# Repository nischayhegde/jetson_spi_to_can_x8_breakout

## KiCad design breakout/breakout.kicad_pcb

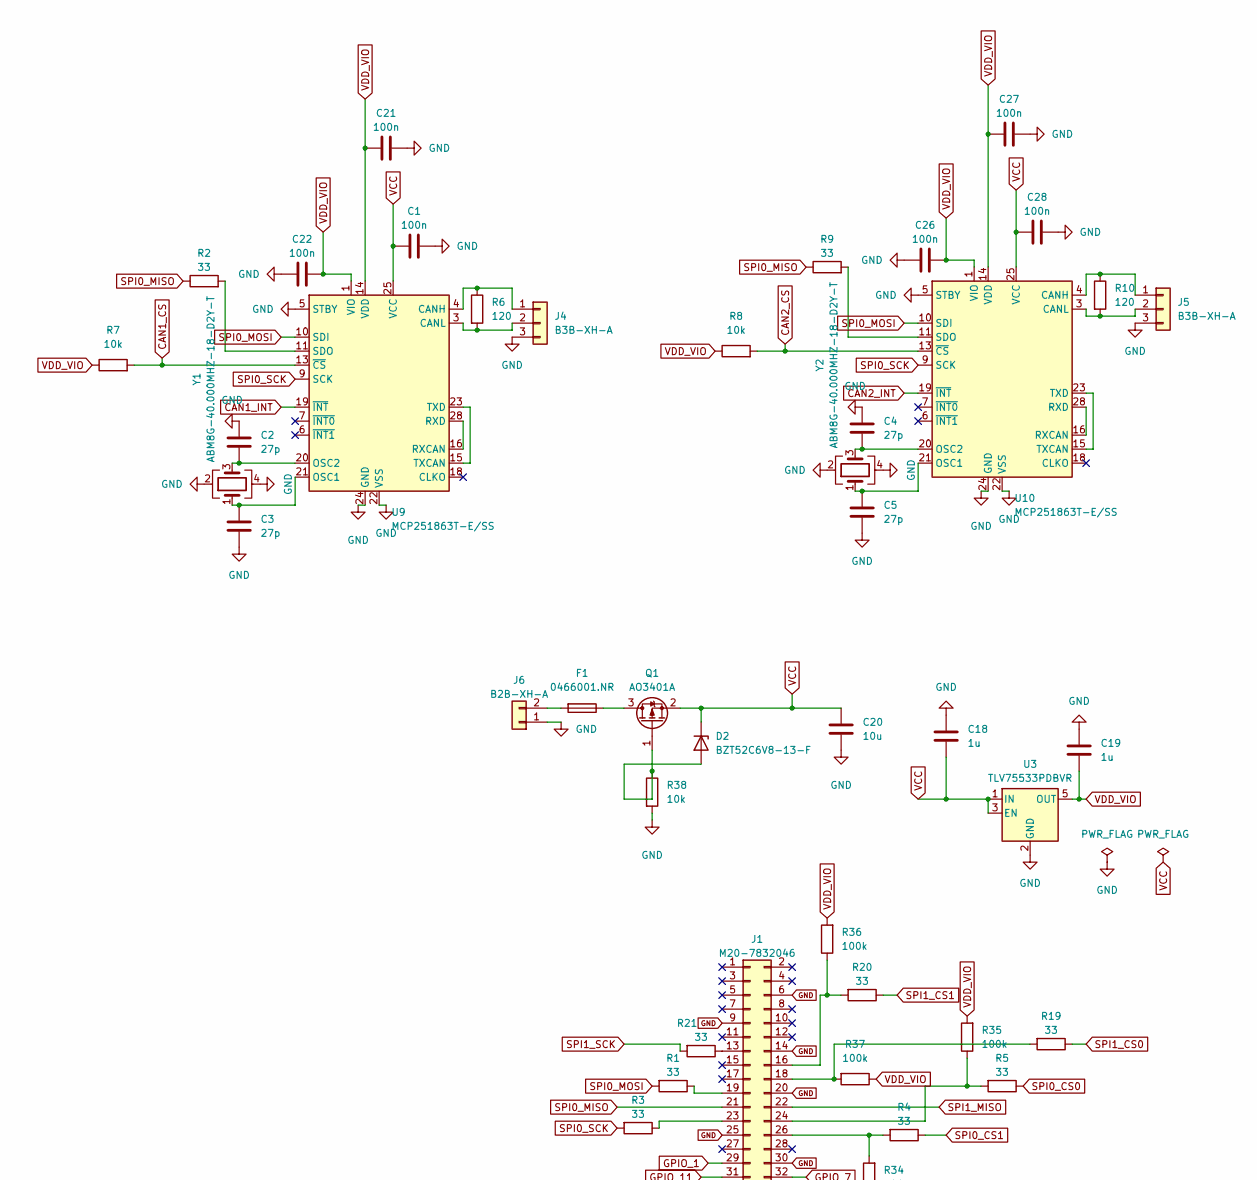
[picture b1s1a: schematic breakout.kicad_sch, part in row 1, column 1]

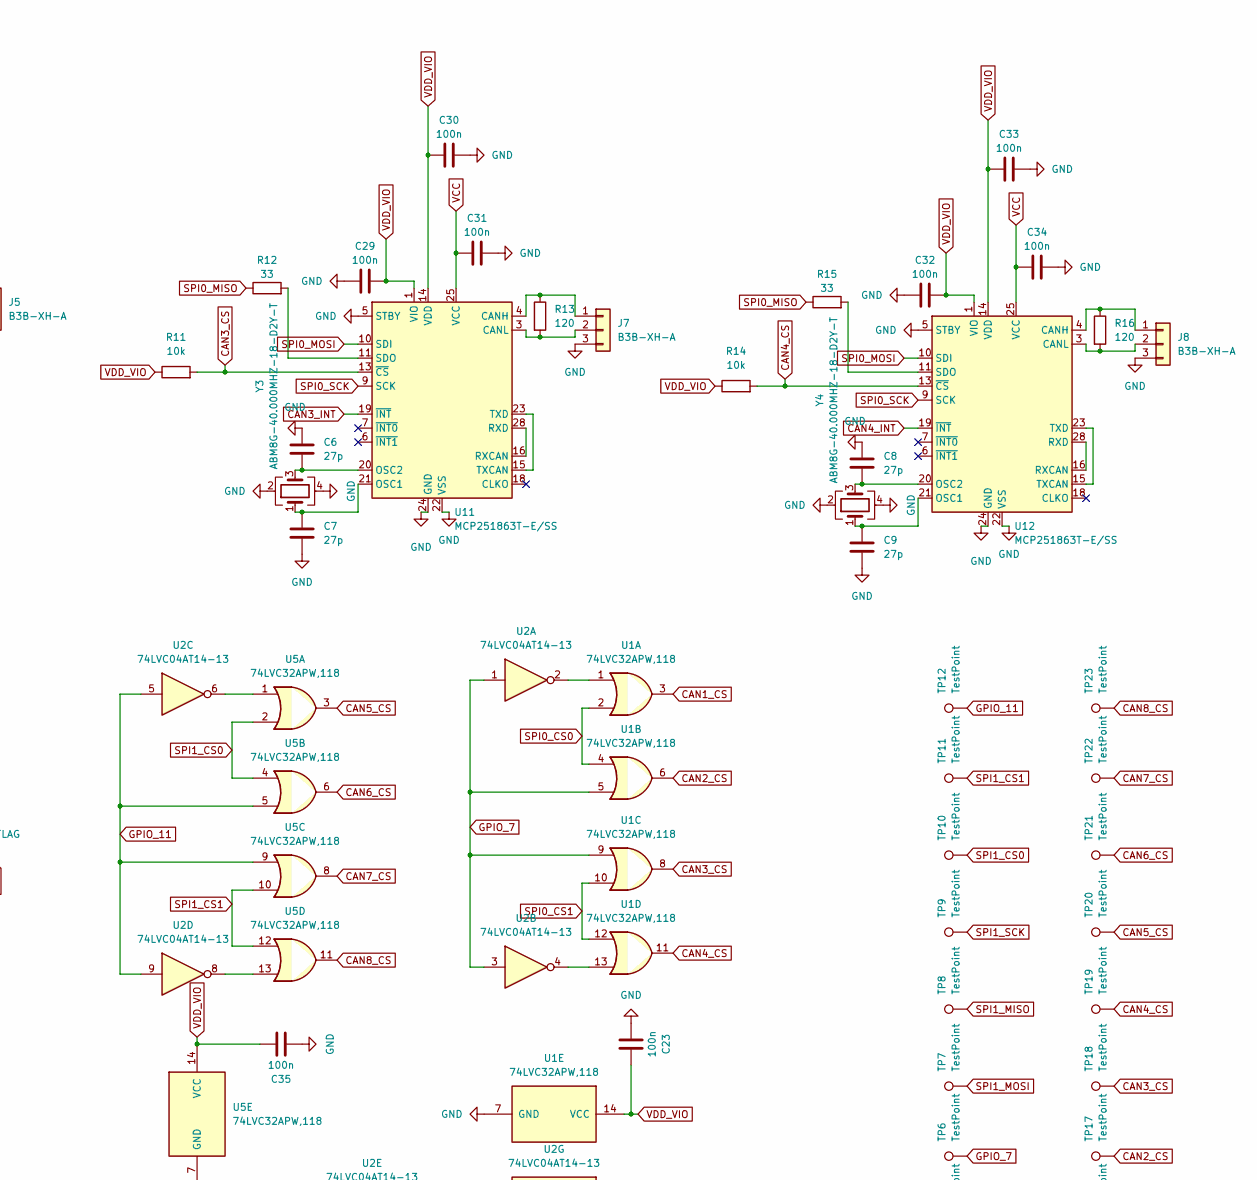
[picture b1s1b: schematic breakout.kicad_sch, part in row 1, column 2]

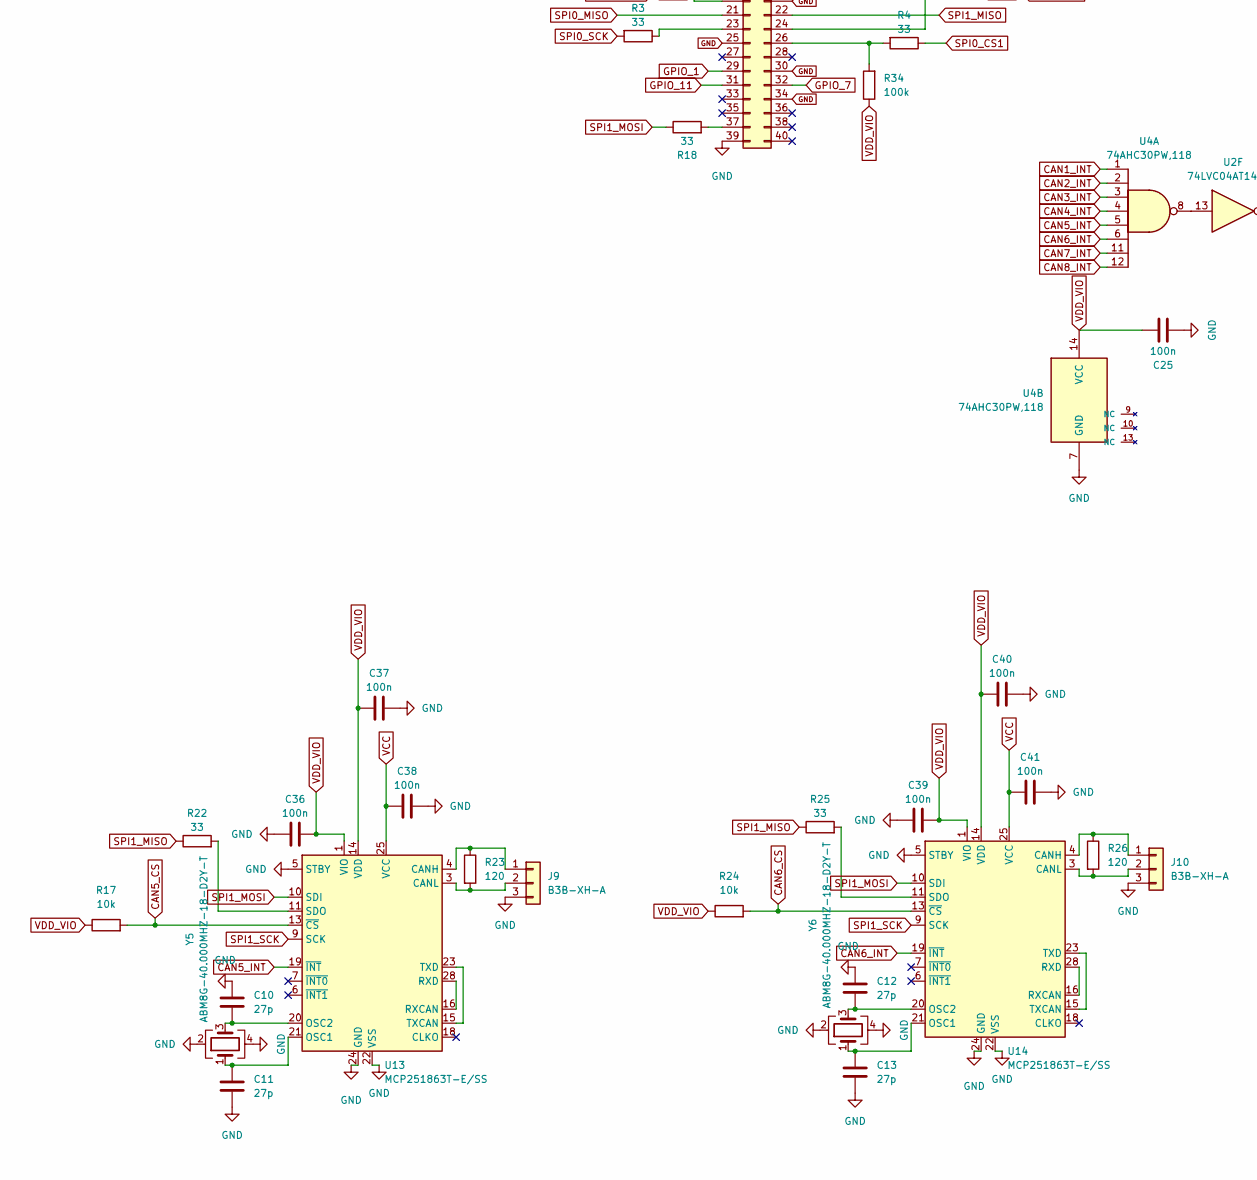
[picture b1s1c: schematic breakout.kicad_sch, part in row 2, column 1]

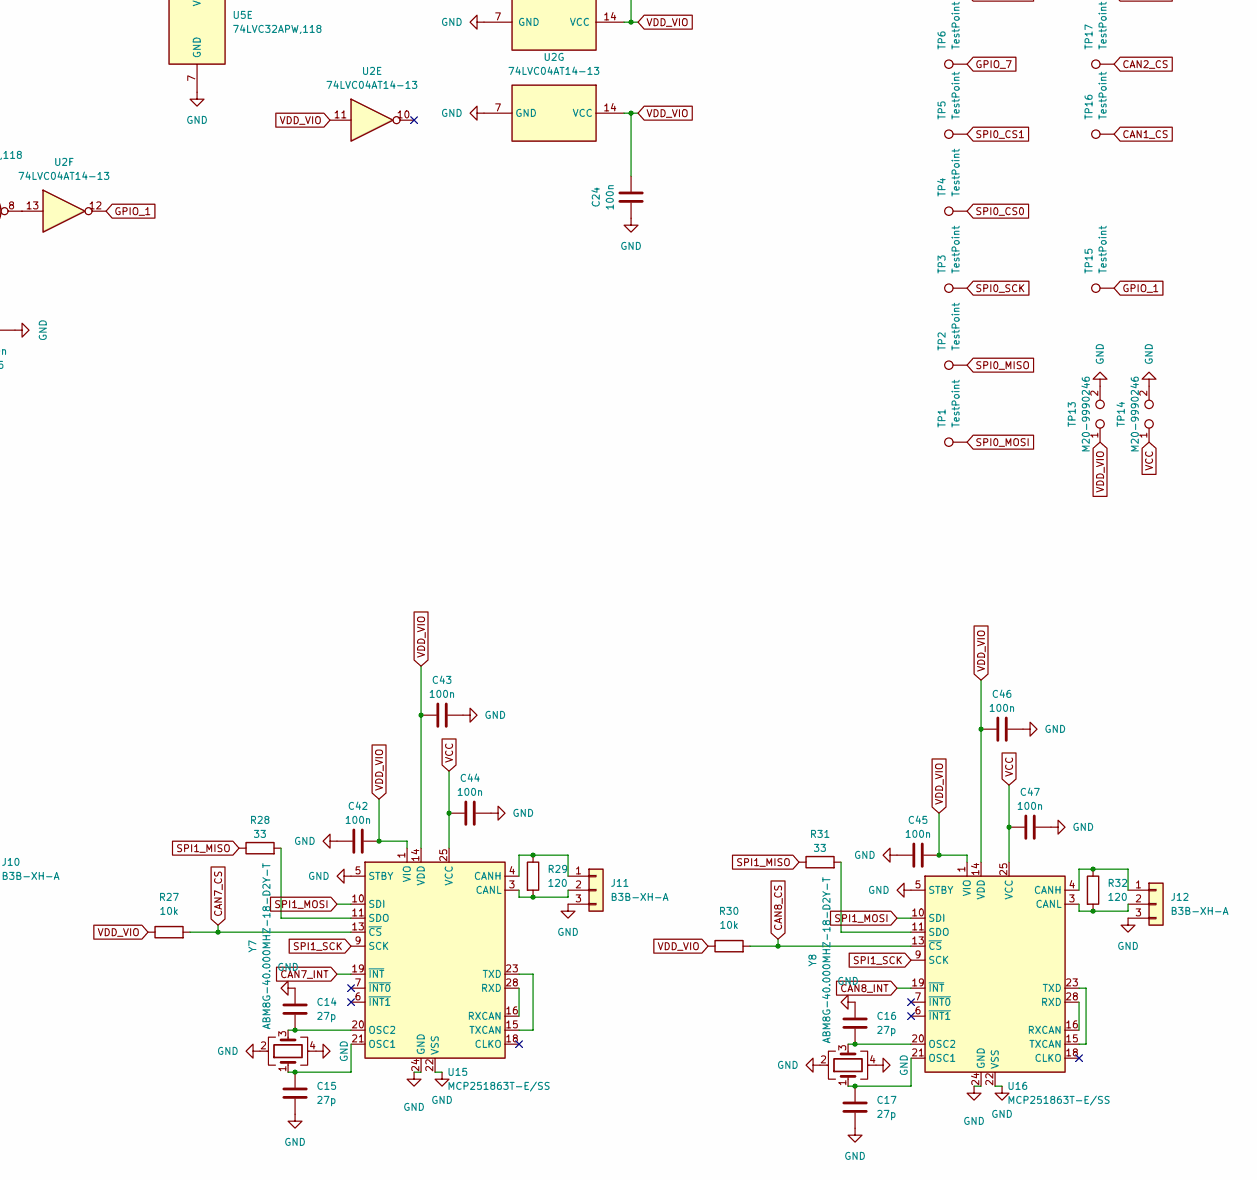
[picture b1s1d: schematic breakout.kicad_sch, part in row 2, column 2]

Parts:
C1, C21, C22, C23, C24, C25, C26, C27, C28, C29, C30, C31, C32, C33, C34, C35, C36, C37, C38, C39, C40, C41, C42, C43, C44, C45, C46, C47: 100n; C_0603_1608Metric; MPN CC0603KRX7R9BB104
C2, C3, C4, C5, C6, C7, C8, C9, C10, C11, C12, C13, C14, C15, C16, C17: 27p; C_0603_1608Metric; MPN CL10C270JB8NNNC
C18, C19: 1u; C_0603_1608Metric; MPN CGA3E1X7R1E105K080AC
C20: 10u; C_0805_2012Metric; MPN CL21B106KOQNNNE
D2: BZT52C6V8-13-F; D_SOD-123; MPN BZT52C6V8-13-F
F1: 0466001.NR; Fuse_1206_3216Metric; MPN 0466001.NR
J1: M20-7832046; PinSocket_2x20_P2.54mm_Vertical; MPN M20-7832046
J4, J5, J7, J8, J9, J10, J11, J12: B3B-XH-A; JST_XH_B3B-XH-A_1x03_P2.50mm_Vertical; MPN B3B-XH-A
J6: B2B-XH-A; JST_XH_B2B-XH-A_1x02_P2.50mm_Vertical; MPN B2B-XH-A
Q1: AO3401A; SOT-23; MPN AO3401A
R1, R2, R3, R4, R5, R9, R12, R15, R18, R19, R20, R21, R22, R25, R28, R31: 33; R_0603_1608Metric; MPN RC0603FR-0733RL
R6, R10, R13, R16, R23, R26, R29, R32: 120; R_1206_3216Metric; MPN RC1206FR-07120RL
R7, R8, R11, R14, R17, R24, R27, R30, R38: 10k; R_0603_1608Metric; MPN RC0603FR-0710KL
R34, R35, R36, R37: 100k; R_0603_1608Metric; MPN RC0603FR-07100KL
TP1, TP2, TP3, TP4, TP5, TP6, TP7, TP8, TP9, TP10, TP11, TP12, TP15, TP16, TP17, TP18, TP19, TP20, TP21, TP22, TP23: TestPoint; TestPoint_Pad_D1.5mm
TP13, TP14: M20-9990246; PinHeader_1x02_P2.54mm_Vertical; MPN M20-9990246
U1, U5: 74LVC32APW,118; TSSOP-14_4.4x5mm_P0.65mm; MPN 74LVC32APW,118
U2: 74LVC04AT14-13; TSSOP-14_4.4x5mm_P0.65mm; MPN 74LVC04AT14-13
U3: TLV75533PDBVR; SOT-23-5; MPN TLV75533PDBVR
U4: 74AHC30PW,118; TSSOP-14_4.4x5mm_P0.65mm; MPN 74AHC30PW,118
U9, U10, U11, U12, U13, U14, U15, U16: MCP251863T-E/SS; SSOP-28_5.3x10.2mm_P0.65mm; MPN MCP251863T-E/SS
Y1, Y2, Y3, Y4, Y5, Y6, Y7, Y8: ABM8G-40.000MHZ-18-D2Y-T; Crystal_SMD_Abracon_ABM8G-4Pin_3.2x2.5mm; MPN ABM8G-40.000MHZ-18-D2Y-T

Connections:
CAN1_CS: R7.2, TP16.1 (1_1), U1.3, U9.13 (~CS)
CAN1_INT: U4.1, U9.19 (~INT)
CAN2_CS: R8.2, TP17.1 (1_1), U1.6, U10.13 (~CS)
CAN2_INT: U4.2, U10.19 (~INT)
CAN3_CS: R11.2, TP18.1 (1_1), U1.8, U11.13 (~CS)
CAN3_INT: U4.3, U11.19 (~INT)
CAN4_CS: R14.2, TP19.1 (1_1), U1.11, U12.13 (~CS)
CAN4_INT: U4.4, U12.19 (~INT)
CAN5_CS: R17.2, TP20.1 (1_1), U5.3, U13.13 (~CS)
CAN5_INT: U4.5, U13.19 (~INT)
CAN6_CS: R24.2, TP21.1 (1_1), U5.6, U14.13 (~CS)
CAN6_INT: U4.6, U14.19 (~INT)
CAN7_CS: R27.2, TP22.1 (1_1), U5.8, U15.13 (~CS)
CAN7_INT: U4.11, U15.19 (~INT)
CAN8_CS: R30.2, TP23.1 (1_1), U5.11, U16.13 (~CS)
CAN8_INT: U4.12, U16.19 (~INT)
GND: C1.1, C2.1, C3.2, C4.1, C5.2, C6.1, C7.2, C8.1, C9.2, C10.1, C11.2, C12.1, C13.2, C14.1, C15.2, C16.1, C17.2, C18.1, C19.1, C20.2, C21.1, C22.2, C23.2, C24.2, C25.2, C26.2, C27.1, C28.1, C29.2, C30.1, C31.1, C32.2, C33.1, C34.1, C35.2, C36.2, C37.1, C38.1, C39.2, C40.1, C41.1, C42.2, C43.1, C44.1, C45.2, C46.1, C47.1, J1.6, J1.9, J1.14, J1.20, J1.25, J1.30, J1.34, J1.39, J4.3, J5.3, J6.1, J7.3, J8.3, J9.3, J10.3, J11.3, J12.3, R38.2, TP13.2, TP14.2, U1.7 (GND), U2.7 (GND), U3.2 (GND), U4.7 (GND), U5.7 (GND), U9.5 (STBY), U9.22 (VSS), U9.24 (GND), U10.5 (STBY), U10.22 (VSS), U10.24 (GND), U11.5 (STBY), U11.22 (VSS), U11.24 (GND), U12.5 (STBY), U12.22 (VSS), U12.24 (GND), U13.5 (STBY), U13.22 (VSS), U13.24 (GND), U14.5 (STBY), U14.22 (VSS), U14.24 (GND), U15.5 (STBY), U15.22 (VSS), U15.24 (GND), U16.5 (STBY), U16.22 (VSS), U16.24 (GND), Y1.2, Y1.4, Y2.2, Y2.4, Y3.2, Y3.4, Y4.2, Y4.4, Y5.2, Y5.4, Y6.2, Y6.4, Y7.2, Y7.4, Y8.2, Y8.4
GPIO_1: J1.29, TP15.1 (1_1), U2.12
GPIO_7: J1.32, TP6.1 (1_1), U1.5, U1.9, U2.1, U2.3
GPIO_11: J1.31, TP12.1 (1_1), U2.5, U2.9, U5.5, U5.9
unnamed: D2.2 (A), Q1.1 (G), R38.1
unnamed: J1.13, R21.1
unnamed: J1.16, R20.2, R36.1
unnamed: J1.18, R19.2, R37.2
unnamed: J1.19, R1.1
unnamed: J1.23, R3.1
unnamed: J1.24, R5.2, R35.1
unnamed: J1.26, R4.2, R34.2
unnamed: J1.37, R18.2
unnamed: J4.1, R6.1, U9.4 (CANH)
unnamed: J4.2, R6.2, U9.3 (CANL)
unnamed: J5.1, R10.1, U10.4 (CANH)
unnamed: J5.2, R10.2, U10.3 (CANL)
unnamed: F1.2, J6.2
unnamed: J7.1, R13.1, U11.4 (CANH)
unnamed: J7.2, R13.2, U11.3 (CANL)
unnamed: J8.1, R16.1, U12.4 (CANH)
unnamed: J8.2, R16.2, U12.3 (CANL)
unnamed: J9.1, R23.1, U13.4 (CANH)
unnamed: J9.2, R23.2, U13.3 (CANL)
unnamed: J10.1, R26.1, U14.4 (CANH)
unnamed: J10.2, R26.2, U14.3 (CANL)
unnamed: J11.1, R29.1, U15.4 (CANH)
unnamed: J11.2, R29.2, U15.3 (CANL)
unnamed: J12.1, R32.1, U16.4 (CANH)
unnamed: J12.2, R32.2, U16.3 (CANL)
unnamed: F1.1, Q1.3 (D)
unnamed: U1.1, U2.2
unnamed: U1.13, U2.4
unnamed: U2.6, U5.1
unnamed: U2.8, U5.13
unnamed: U2.13, U4.8
unnamed: C3.1, U9.21 (OSC1), Y1.1
unnamed: C2.2, U9.20 (OSC2), Y1.3
unnamed: U9.16 (RXCAN), U9.28 (RXD)
unnamed: R2.2, U9.11 (SDO)
unnamed: U9.15 (TXCAN), U9.23 (TXD)
unnamed: C5.1, U10.21 (OSC1), Y2.1
unnamed: C4.2, U10.20 (OSC2), Y2.3
unnamed: U10.16 (RXCAN), U10.28 (RXD)
unnamed: R9.2, U10.11 (SDO)
unnamed: U10.15 (TXCAN), U10.23 (TXD)
unnamed: C7.1, U11.21 (OSC1), Y3.1
unnamed: C6.2, U11.20 (OSC2), Y3.3
unnamed: U11.16 (RXCAN), U11.28 (RXD)
unnamed: R12.2, U11.11 (SDO)
unnamed: U11.15 (TXCAN), U11.23 (TXD)
unnamed: C9.1, U12.21 (OSC1), Y4.1
unnamed: C8.2, U12.20 (OSC2), Y4.3
unnamed: U12.16 (RXCAN), U12.28 (RXD)
unnamed: R15.2, U12.11 (SDO)
unnamed: U12.15 (TXCAN), U12.23 (TXD)
unnamed: C11.1, U13.21 (OSC1), Y5.1
unnamed: C10.2, U13.20 (OSC2), Y5.3
unnamed: U13.16 (RXCAN), U13.28 (RXD)
unnamed: R22.2, U13.11 (SDO)
unnamed: U13.15 (TXCAN), U13.23 (TXD)
unnamed: C13.1, U14.21 (OSC1), Y6.1
unnamed: C12.2, U14.20 (OSC2), Y6.3
unnamed: U14.16 (RXCAN), U14.28 (RXD)
unnamed: R25.2, U14.11 (SDO)
unnamed: U14.15 (TXCAN), U14.23 (TXD)
unnamed: C15.1, U15.21 (OSC1), Y7.1
unnamed: C14.2, U15.20 (OSC2), Y7.3
unnamed: U15.16 (RXCAN), U15.28 (RXD)
unnamed: R28.2, U15.11 (SDO)
unnamed: U15.15 (TXCAN), U15.23 (TXD)
unnamed: C17.1, U16.21 (OSC1), Y8.1
unnamed: C16.2, U16.20 (OSC2), Y8.3
unnamed: U16.16 (RXCAN), U16.28 (RXD)
unnamed: R31.2, U16.11 (SDO)
unnamed: U16.15 (TXCAN), U16.23 (TXD)
SPI0_CS0: R5.1, TP4.1 (1_1), U1.2, U1.4
SPI0_CS1: R4.1, TP5.1 (1_1), U1.10, U1.12
SPI0_MISO: J1.21, R2.1, R9.1, R12.1, R15.1, TP2.1 (1_1)
SPI0_MOSI: R1.2, TP1.1 (1_1), U9.10 (SDI), U10.10 (SDI), U11.10 (SDI), U12.10 (SDI)
SPI0_SCK: R3.2, TP3.1 (1_1), U9.9 (SCK), U10.9 (SCK), U11.9 (SCK), U12.9 (SCK)
SPI1_CS0: R19.1, TP10.1 (1_1), U5.2, U5.4
SPI1_CS1: R20.1, TP11.1 (1_1), U5.10, U5.12
SPI1_MISO: J1.22, R22.1, R25.1, R28.1, R31.1, TP8.1 (1_1)
SPI1_MOSI: R18.1, TP7.1 (1_1), U13.10 (SDI), U14.10 (SDI), U15.10 (SDI), U16.10 (SDI)
SPI1_SCK: R21.2, TP9.1 (1_1), U13.9 (SCK), U14.9 (SCK), U15.9 (SCK), U16.9 (SCK)
VCC: C1.2, C18.2, C20.1, C28.2, C31.2, C34.2, C38.2, C41.2, C44.2, C47.2, D2.1 (K), Q1.2 (S), TP14.1, U3.1 (IN), U3.3 (EN), U9.25 (VCC), U10.25 (VCC), U11.25 (VCC), U12.25 (VCC), U13.25 (VCC), U14.25 (VCC), U15.25 (VCC), U16.25 (VCC)
VDD_VIO: C19.2, C21.2, C22.1, C23.1, C24.1, C25.1, C26.1, C27.2, C29.1, C30.2, C32.1, C33.2, C35.1, C36.1, C37.2, C39.1, C40.2, C42.1, C43.2, C45.1, C46.2, R7.1, R8.1, R11.1, R14.1, R17.1, R24.1, R27.1, R30.1, R34.1, R35.2, R36.2, R37.1, TP13.1, U1.14 (VCC), U2.11, U2.14 (VCC), U3.5 (OUT), U4.14 (VCC), U5.14 (VCC), U9.1 (VIO), U9.14 (VDD), U10.1 (VIO), U10.14 (VDD), U11.1 (VIO), U11.14 (VDD), U12.1 (VIO), U12.14 (VDD), U13.1 (VIO), U13.14 (VDD), U14.1 (VIO), U14.14 (VDD), U15.1 (VIO), U15.14 (VDD), U16.1 (VIO), U16.14 (VDD)

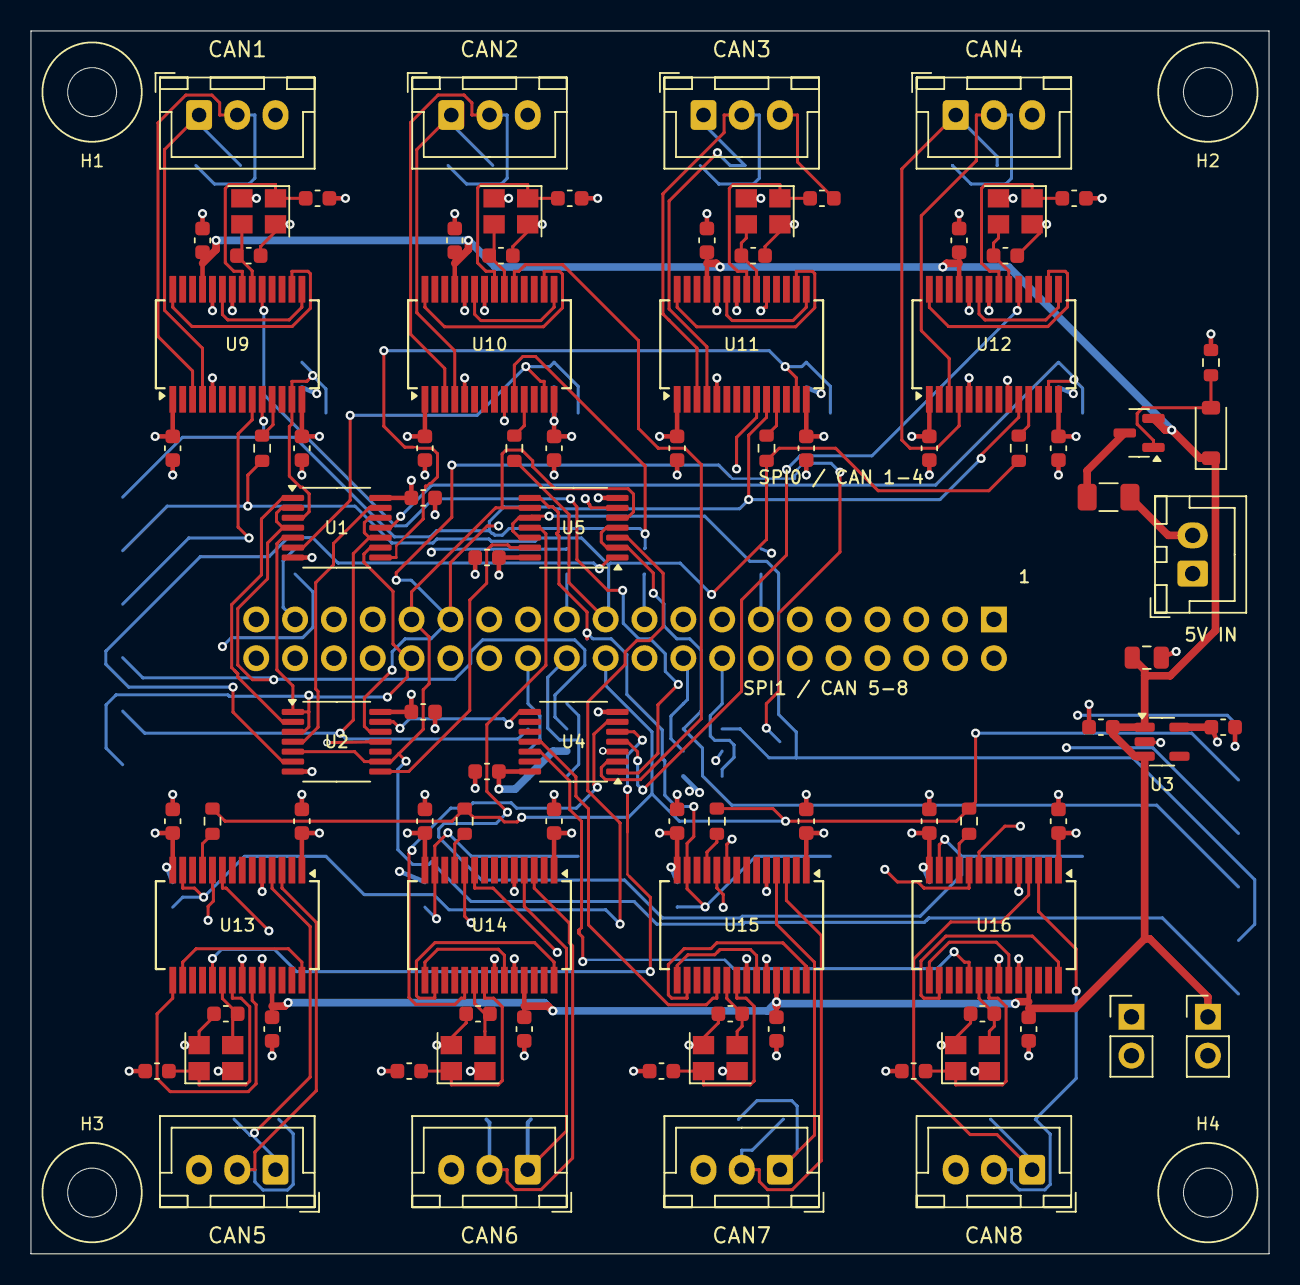
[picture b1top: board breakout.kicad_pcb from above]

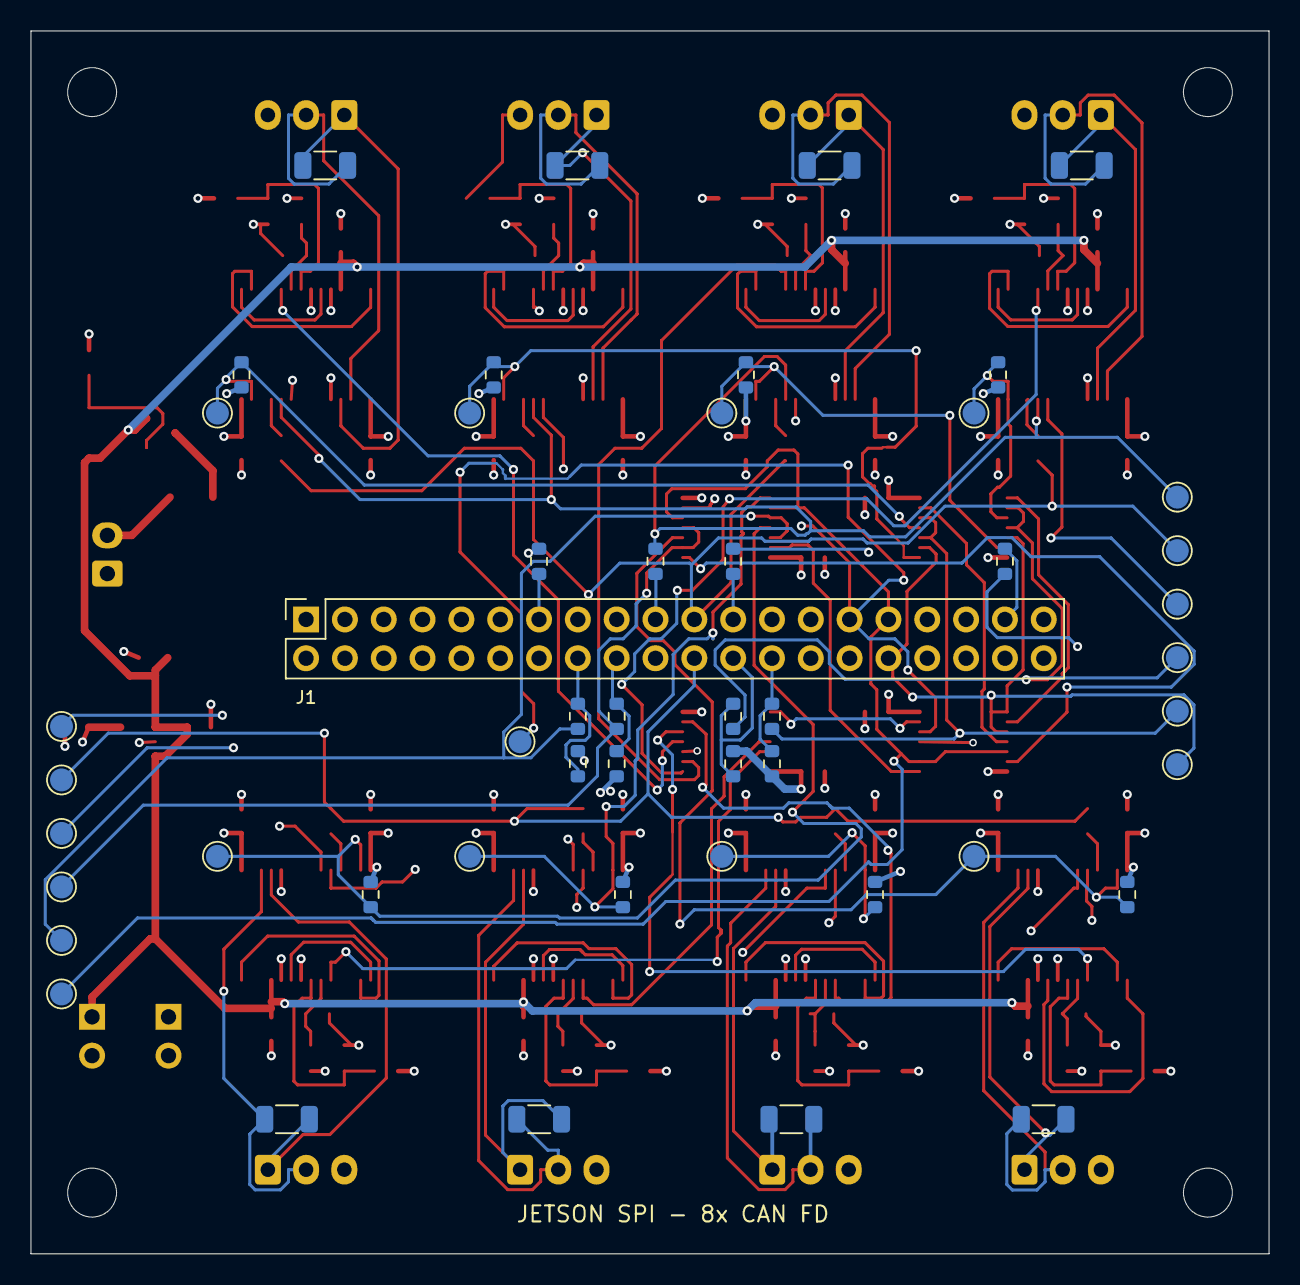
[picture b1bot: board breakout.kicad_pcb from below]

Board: 4 copper layers, 81.0 x 80.0 mm, 145 parts (50 on the bottom side), 104 nets.

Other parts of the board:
H1, H2, H3, H4: M3 mounting hole; MountingHole_3.2mm_M3_7mm_Keepout

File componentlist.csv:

mpn,manufacturer,quantity,schematic_quantity,board_quantity,placed_references,design_value,footprint,function,specifications,status,mouser_url,digikey_url,notes
MCP251863T-E/SS,Microchip,8,8,8,U9;U10;U11;U12;U13;U14;U15;U16,MCP251863T-E/SS,BreakoutBoard:SSOP-28_5.3x10.2mm_P0.65mm,CAN controller/transceiver,"SPI CAN FD controller plus transceiver; SSOP-28; VDD/VIO=3.3 V, VCC=5 V",PLACED,https://www.mouser.com/en/ProductDetail/Microchip-Technology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,https://www.digikey.com/en/products/detail/microchip-technol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,
ABM8G-40.000MHZ-18-D2Y-T,Abracon,8,8,8,Y1;Y2;Y3;Y4;Y5;Y6;Y7;Y8,ABM8G-40.000MHZ-18-D2Y-T,BreakoutBoard:Crystal_SMD_Abracon_ABM8G-4Pin_3.2x2.5mm,40 MHz crystal,Passive crystal; CL=18 pF; grounded case pads; 3.2 x 2.5 mm,PLACED,https://www.mouser.com/en/ProductDetail/ABRACON/ABM8G-40.000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,https://www.digikey.com/en/products/detail/abracon-llc/ABM8G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,
TLV75533PDBVR,Texas Instruments,1,1,1,U3,TLV75533PDBVR,BreakoutBoard:SOT-23-5,3.3 V LDO,"Fixed 3.3 V, 500 mA; SOT-23-5 / DBV",PLACED,https://www.mouser.com/en/ProductDetail/Texas-Instruments/TL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,https://www.digikey.com/en/products/detail/texas-instruments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,
CL10C270JB8NNNC,Samsung Electro-Mechanics,16,16,16,C2;C3;C4;C5;C6;C7;C8;C9;C10;C11;C12;C13;C14;C15;C16;C17,27p,Capacitor_SMD:C_0603_1608Metric,Crystal load capacitor,"27 pF, +/-5%, C0G/NP0, 50 V, 0603",PLACED,https://www.mouser.it/ProductDetail/Samsung-Electro-Mechanic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,https://www.digikey.com/en/products/detail/samsung-electro-m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,
CC0603KRX7R9BB104,YAGEO,28,28,28,C1;C21;C22;C23;C24;C25;C26;C27;C28;C29;C30;C31;C32;C33;C34;C35;C36;C37;C38;C39;C40;C41;C42;C43;C44;C45;C46;C47,100n,BreakoutBoard:C_0603_1608Metric,Local bypass capacitor,"100 nF, +/-10%, X7R, 50 V, 0603",PLACED,https://www.mouser.com/en/ProductDetail/YAGEO/CC0603KRX7R9BB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,https://www.digikey.com/en/products/detail/yageo/CC0603KRX7R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,28 x 100 nF bypass capacitors: C1 and C21-C47. MPN retained in hidden fields.
CGA3E1X7R1E105K080AC,TDK,2,2,2,C18;C19,1u,BreakoutBoard:C_0603_1608Metric,LDO input/output capacitor,"1 uF, +/-10%, X7R, 25 V, 0603",PLACED,https://www.mouser.com/en/ProductDetail/TDK/CGA3E1X7R1E105K0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,https://www.digikey.com/en/products/detail/tdk/CGA3E1X7R1E10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,
CL21B106KOQNNNE,Samsung Electro-Mechanics,1,1,1,C20,10u,BreakoutBoard:C_0805_2012Metric,Protected-input bulk capacitor,"10 uF, +/-10%, X7R, 16 V, 0805",PLACED,https://www.mouser.com/en/ProductDetail/Samsung-Electro-Mech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,https://www.digikey.com/en/products/detail/samsung-electro-m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,
RC1206FR-07120RL,YAGEO,8,8,8,R6;R10;R13;R16;R23;R26;R29;R32,120,BreakoutBoard:R_1206_3216Metric,Fixed CAN termination,"120 ohm, +/-1%, 0.25 W, 1206",PLACED,https://www.mouser.com/en/ProductDetail/YAGEO/RC1206FR-07120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,https://www.digikey.com/en/products/detail/yageo/RC1206FR-07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,"All eight CAN termination resistors use this 1206, 120-ohm, 1%, 0.25 W part. Order 10 instead of 8: the quantity discount lowers the line total."
RC0603FR-0710KL,YAGEO,9,9,9,R7;R8;R11;R14;R17;R24;R27;R30;R38,10k,BreakoutBoard:R_0603_1608Metric,CAN nCS pull-ups / MOSFET gate pull-down,"10 kohm, +/-1%, 0.1 W, 0603",PLACED,https://www.mouser.com/en/ProductDetail/603-RC0603FR-0710KL,https://www.digikey.com/en/products/detail/yageo/RC0603FR-07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,Order 10 instead of 9: the quantity discount lowers the line total.
RC0603FR-07100KL,YAGEO,4,4,4,R34;R35;R36;R37,100k,BreakoutBoard:R_0603_1608Metric,Native Jetson CS pull-ups,"100 kohm, +/-1%, 0.1 W, 0603",PLACED,https://www.mouser.com/en/ProductDetail/YAGEO/RC0603FR-07100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,https://www.digikey.com/en/products/detail/yageo/RC0603FR-07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,Order 10 instead of 4: the quantity discount lowers the line total.
RC0603FR-0733RL,YAGEO,16,16,16,R1;R2;R3;R4;R5;R9;R12;R15;R18;R19;R20;R21;R22;R25;R28;R31,33,BreakoutBoard:R_0603_1608Metric,SPI series damping,"33 ohm, +/-1%, 0.1 W, 0603",PLACED,https://www.mouser.com/en/ProductDetail/YAGEO/RC0603FR-0733R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,https://www.digikey.com/en/products/detail/yageo/RC0603FR-07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,
B3B-XH-A,JST,8,8,8,J4;J5;J7;J8;J9;J10;J11;J12,B3B-XH-A,BreakoutBoard:JST_XH_B3B-XH-A_1x03_P2.50mm_Vertical,CAN connector,"3 positions, 2.50 mm pitch, vertical through-hole XH header",PLACED,https://www.mouser.com/en/ProductDetail/JST-Commercial/B3B-X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,https://www.digikey.com/en/products/detail/jst-sales-america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,
B2B-XH-A,JST,1,1,1,J6,B2B-XH-A,BreakoutBoard:JST_XH_B2B-XH-A_1x02_P2.50mm_Vertical,5 V input connector,"2 positions, 2.50 mm pitch, vertical through-hole XH header",PLACED,https://www.mouser.com/en/ProductDetail/JST-Commercial/B2B-X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,https://www.digikey.com/en/products/detail/jst-sales-america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,
M20-7832046,Harwin,1,1,1,J1,M20-7832046,Connector_PinSocket_2.54mm:PinSocket_2x20_P2.54mm_Vertical,Jetson 40-pin female socket,"Female 2 x 20, 2.54 mm pitch, vertical through-hole; 8.5 mm above PCB; tin contacts",PLACED,https://www.mouser.com/en/ProductDetail/Harwin/M20-7832046?q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,https://www.digikey.com/en/products/detail/harwin-inc/M20-78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,"J1 consistently uses M20-7832046 and the female socket footprint in the schematic, PCB and order list."
0466001.NR,Littelfuse,1,1,1,F1,0466001.NR,BreakoutBoard:Fuse_1206_3216Metric,Series input fuse,"1 A, 63 V AC/DC, fast acting, 1206",PLACED,https://www.mouser.com/en/ProductDetail/Littelfuse/0466001.N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,https://www.digikey.com/en/products/detail/littelfuse-inc/04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,F1 is fitted in the current schematic and layout.
AO3401A,Alpha & Omega Semiconductor,1,1,1,Q1,AO3401A,BreakoutBoard:SOT-23,Reverse-hookup MOSFET,"P-channel, -30 V, VGS absolute maximum +/-12 V, SOT-23",PLACED,https://www.mouser.com/c/?q=AO3401A,https://www.digikey.com/en/products/detail/alpha-omega-semic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,Keep Alpha & Omega AO3401A. No alternate MOSFET selected.
BZT52C6V8-13-F,Diodes Incorporated,1,1,1,D2,BZT52C6V8-13-F,BreakoutBoard:D_SOD-123,MOSFET gate-source clamp,"6.8 V Zener, SOD-123; not a 5 V rail clamp",PLACED,https://www.mouser.com/en/ProductDetail/Diodes-Incorporated/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,https://www.digikey.com/en/products/detail/diodes-incorporat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,
"74AHC30PW,118",Nexperia,1,1,1,U4,"74AHC30PW,118",BreakoutBoard:TSSOP-14_4.4x5mm_P0.65mm,Shared interrupt NAND,"8-input NAND, TSSOP-14; powered at 3.3 V",PLACED,https://www.mouser.com/ProductDetail/Nexperia/74AHC30PW118?q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,https://www.digikey.com/en/products/detail/nexperia-usa-inc/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,
"74LVC32APW,118",Nexperia,2,2,2,U1;U5,"74LVC32APW,118",BreakoutBoard:TSSOP-14_4.4x5mm_P0.65mm,Chip-select bank OR gates,"Quad 2-input OR, TSSOP-14; powered at 3.3 V",PLACED,https://www.mouser.com/en/ProductDetail/Nexperia/74LVC32APW1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,https://www.digikey.com/en/products/detail/nexperia-usa-inc/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,
74LVC04AT14-13,Diodes Incorporated,1,1,1,U2,74LVC04AT14-13,BreakoutBoard:TSSOP-14_4.4x5mm_P0.65mm,Bank / shared-IRQ inverters,"Hex NOT, TSSOP-14; powered at 3.3 V",PLACED,https://www.mouser.com/ProductDetail/Diodes-Incorporated/74L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,https://www.digikey.com/en/products/detail/diodes-incorporat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,
M20-9990246,Harwin,2,2,2,TP13;TP14,M20-9990246,Connector_PinHeader_2.54mm:PinHeader_1x02_P2.54mm_Vertical,Two-pin test header,"Male 1 x 2, 2.54 mm pitch, vertical through-hole; 0.64 mm square pins; 3 mm solder tails",PLACED,https://www.mouser.com/en/ProductDetail/Harwin/M20-9990246?q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,https://www.digikey.com/en/products/detail/harwin-inc/M20-99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,Fitted headers for TP13 and TP14. The other 21 test points are bare PCB pads.

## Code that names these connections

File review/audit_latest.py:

"""Audit the saved schematic's KiCad XML export; never edits the design."""
from pathlib import Path
from collections import Counter
import csv
import hashlib
import itertools
import json
import xml.etree.ElementTree as ET

ROOT = Path(__file__).resolve().parent
OUT = ROOT / 'latest'
SCHEMATIC = ROOT.parent / 'breakout' / 'breakout.kicad_sch'
tree = ET.parse(OUT / 'breakout.net.xml').getroot()
components = {c.attrib['ref']: c for c in tree.findall('./components/comp')}
pin_net = {(n.attrib['ref'], n.attrib['pin']): net.attrib['name']
           for net in tree.findall('./nets/net') for n in net.findall('node')}


def net(ref, pin):
    return pin_net.get((ref, str(pin)), 'MISSING')


def value(ref):
    return components[ref].findtext('value')


def pair(ref):
    return {net(ref, 1), net(ref, 2)}


def series_destination(ref, pin, resistance='33'):
    source = net(ref, pin)
    found = []
    for name in components:
        if name.startswith('R') and value(name) == resistance and source in pair(name):
            found.append((name, next(iter(pair(name) - {source}), source)))
    return found


rows = []
for channel, number in enumerate(range(9, 17), 1):
    ref = f'U{number}'
    bus = 0 if channel <= 4 else 1
    crystal = f'Y{channel}'
    connector = f'J{[4,5,7,8,9,10,11,12][channel-1]}'
    termination = f'R{[6,10,13,16,23,26,29,32][channel-1]}'
    cap_numbers = [[1,2,3],[8,9,10],[11,12,13],[14,15,16],
                   [18,19,20],[21,22,23],[24,25,26],[27,28,29]][channel-1]
    cap_pairs = [pair(f'CC0603KRX7R9BB{n}') for n in cap_numbers]
    result = dict(channel=channel, reference=ref, expected_spi=bus,
                  VCC_pin25=net(ref,25), VDD_pin14=net(ref,14), VIO_pin1=net(ref,1),
                  SCK_pin9=net(ref,9), SDI_pin10=net(ref,10),
                  SDO_via_resistor=series_destination(ref,11),
                  CS_pin13=net(ref,13), INT_pin19=net(ref,19))
    result['checks'] = {
        'power': net(ref,25) == net('U3',1) == net('Q1',2)
                 and net(ref,14) == net(ref,1) == net('U3',5),
        'spi': net(ref,9) == f'SPI{bus}_SCK' and net(ref,10) == f'SPI{bus}_MOSI'
               and len(result['SDO_via_resistor']) == 1
               and result['SDO_via_resistor'][0][1] == f'SPI{bus}_MISO',
        'chip_select': net(ref,13) == f'CAN{channel}_CS',
        'interrupt': net(ref,19) == f'CAN{channel}_INT',
        'internal_can_links': net(ref,15) == net(ref,23) and net(ref,28) == net(ref,16),
        'grounds_and_standby': net(ref,22) == net(ref,24) == net(ref,5) == 'GND',
        'crystal': net(crystal,1) == net(ref,21) and net(crystal,3) == net(ref,20)
                   and net(crystal,2) == net(crystal,4) == 'GND',
        'crystal_capacitors': all(any(c.find('libsource').attrib == components[f'C{2*channel}'].find('libsource').attrib
                                    and c.findtext('value') == '27p'
                                    and pair(c.attrib['ref']) == {net(ref,pin),'GND'}
                                    for c in components.values() if c.attrib['ref'].startswith('C'))
                                 for pin in (20,21)),
        'local_bypass': cap_pairs.count({'GND',net('U3',1)}) == 1
                        and cap_pairs.count({'GND',net('U3',5)}) == 2,
        'can_connector': net(connector,1) == net(ref,4) and net(connector,2) == net(ref,3)
                         and net(connector,3) == 'GND',
        'termination': value(termination) == '120'
                       and pair(termination) == {net(ref,3),net(ref,4)},
    }
    rows.append(result)

gates = {}
for ref in ('U1','U5'):
    for a,b,y in ((1,2,3),(4,5,6),(9,10,8),(12,13,11)):
        gates[net(ref,y)] = ('OR',net(ref,a),net(ref,b))
for a,y in ((1,2),(3,4),(5,6),(9,8),(11,10),(13,12)):
    gates[net('U2',y)] = ('NOT',net('U2',a))
gates[net('U4',8)] = ('NAND',*(net('U4',p) for p in (1,2,3,4,5,6,11,12)))


def evaluate(name, signals):
    if name in signals:
        return signals[name]
    kind,*inputs = gates[name]
    values = [evaluate(n,signals) for n in inputs]
    return int(not values[0]) if kind == 'NOT' else int(not all(values)) if kind == 'NAND' else int(any(values))


bank_table = []
for bus,bank_name,first in ((0,'GPIO_7',1),(1,'GPIO_11',5)):
    for bank,cs0,cs1 in itertools.product((0,1),repeat=3):
        signals = {bank_name:bank,f'SPI{bus}_CS0':cs0,f'SPI{bus}_CS1':cs1}
        levels = {f'CAN{n}_CS':evaluate(f'CAN{n}_CS',signals) for n in range(first,first+4)}
        bank_table.append(dict(spi=bus,bank=bank,native_cs0=cs0,native_cs1=cs1,
                               forbidden_both_active=cs0==cs1==0,levels=levels,
                               selected=[name for name,v in levels.items() if not v]))
irq_table = []
for states in itertools.product((0,1),repeat=8):
    signals = {f'CAN{i}_INT':v for i,v in enumerate(states,1)}
    irq_table.append(dict(inputs=states,jetson_irq=evaluate('GPIO_1',signals)))

erc_path = OUT / 'erc_after.json'
if not erc_path.exists():
    erc_path = OUT / 'erc_before.json'
violations = [v for sheet in json.loads(erc_path.read_text())['sheets'] for v in sheet['violations']]
summary = dict(
    schematic_sha256=hashlib.sha256(SCHEMATIC.read_bytes()).hexdigest(),
    schematic_unchanged_since_snapshot=hashlib.sha256(SCHEMATIC.read_bytes()).hexdigest()
        == json.loads((OUT/'input_snapshot.json').read_text())['breakout/breakout.kicad_sch']['sha256'],
    component_count=len(components),
    channel_checks=rows,
    all_eight_channel_checks_pass=all(all(row['checks'].values()) for row in rows),
    gate_power={ref:net(ref,14) for ref in ('U1','U2','U4','U5')},
    gate_power_correct=all(net(ref,14)==net('U3',5) for ref in ('U1','U2','U4','U5')),
    gate_bypass_correct=all(pair(f'CC0603KRX7R9BB{n}')=={'GND',net('U3',5)}
                            for n in (5,6,7,17)),
    input_fuses=[ref for ref in components if ref.startswith('F')],
    protection_checks={
        'drain_to_input':net('Q1',3)==net('J6',2),
        'source_to_protected_rail':net('Q1',2)==net('U3',1),
        'zener_cathode_to_source':net('D2',1)==net('Q1',2),
        'zener_anode_to_gate':net('D2',2)==net('Q1',1),
        'gate_pulldown':value('R38')=='10k' and pair('R38')=={net('Q1',1),'GND'},
        'bulk_after_mosfet':value('C20')=='10u' and pair('C20')=={net('Q1',2),'GND'},
        'ldo_input_capacitor':value('C18')=='1u' and pair('C18')=={net('U3',1),'GND'},
        'ldo_output_capacitor':value('C19')=='1u' and pair('C19')=={net('U3',5),'GND'},
    },
    bank_idle_deselects_all=all(not row['selected'] for row in bank_table
                                if row['native_cs0']==row['native_cs1']==1),
    bank_single_select=all(len(row['selected'])==1 for row in bank_table
                           if row['native_cs0']!=row['native_cs1']),
    shared_irq_active_low=all(row['jetson_irq']==int(all(row['inputs'])) for row in irq_table),
    erc_file=erc_path.name,erc_total=len(violations),
    erc_severity_counts=dict(Counter(v['severity'] for v in violations)),
    erc_type_counts=dict(Counter(v['type'] for v in violations)),
    missing_footprints=[ref for ref,c in components.items() if not c.findtext('footprint')],
    header_connected_ground_pins=[p for p in (6,9,14,20,25,30,34,39) if net('J1',p)=='GND'],
)
(OUT/'audit_results.json').write_text(json.dumps(summary,indent=2)+'\n')
(OUT/'bank_truth_table.json').write_text(json.dumps(bank_table,indent=2)+'\n')
(OUT/'irq_truth_table.json').write_text(json.dumps(irq_table,indent=2)+'\n')
with (OUT/'channel_audit.csv').open('w',newline='') as output:
    data=[{**{k:v for k,v in r.items() if k!='checks'},**r['checks']} for r in rows]
    writer=csv.DictWriter(output,fieldnames=data[0]);writer.writeheader();writer.writerows(data)
print(json.dumps({k:v for k,v in summary.items() if k not in ('channel_checks','missing_footprints')},indent=2))
print('Missing footprints:',len(summary['missing_footprints']))
